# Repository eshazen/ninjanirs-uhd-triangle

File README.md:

# ninjanirs-uhd-triangle

### 2026-07-27

Printing 10 pcs `...onshape/UHD_Assembly_Filled_2026-07-13.stl` with .08mm extra fine.

(the other ones are still in the car)

### 2026-07-13

Printing `...onshape/UHD_Assembly_Filled_2026-07-13.stl` with .08mm extra fine.

40m time.

David wants 25 pcs.

### 2026-06-04

Printing UHD_Assembly_Filled
<br>This version has a "hull" shape around the optodes for (much) faster printing and no support headaches

Orient with light pipes facing up, tree support
<br>Two versions:  Standard, and 0.08mm fine

### 2026-05-06

Now working on solid triad for "production" for mechanical test.
<br>See `UHD_Assembly_Filled` in onshape.  Needs a new sketch which
defines a convex hull around the optode features to fill in the body.
Also need to fill the volume below the springtop with a pyramid-like
solid.

Really we need an algorithm which would traverse a range of Z and
generate a 3D hull formed by a 2D hull at each Z.

### 2026-03-20

* Printing second springtop (still 1-up).
<br>Printed two groups of 3 so total (8) pieces now (1 fail so 7 total)
* Printing (4) grommets with brim (2:14)  OK.

### 2026-03-18

Starting production print (some R&D first).
<br>Printing UHD_Assembly_Ver1 as is using 0.4mm nozzle
and profile "0.08mm Extra Fine".  Quoted time 42m.
<br>_If this doesn't work we'll change to 0.2mm nozzle._

Seems OK.  Printing Grommets with same settings.
Also seems ok with some cleanup.

Printing springtop both ways up, same settings.  Broke both but
right-side up seems best if we can manage to get it off the support.
<br>Trying again right-side up.  OK with care

Printing caps with same settings (right-side up).
<br>Caps don't quite fit in springtop.

#### Re-printing all with 0.2mm nozzle

* Printing grommets using "0.06mm High Quality".  Time est 38min
<br>Fails with non-adhered parts

Make some changes as AI suggests:

* Change first layer height to 0.16mm.
* Change bed temp from 55 to 60 for both first and subsequent layers
* Change initial layer speed to 20mm/s
  <br>(in Filament profile)

Did not (yet) try to scrub the plate with dish soap!

Print the grommets again, much better.

Now the optodes, same settings.  Est 1:07.  Ok.

And the caps.  45min.  OK

Springtop:  enlarge hole to 3.75 and drill through the arms.  26m
<br>Print failed (bad adhesion).  Cleaned plate and tried again.  Fail
<br>Change to "0.12mm Standard" and added one layer of raft.  Fail.

Probably need to print these with 0.5mm nozzle?  Or somehow create a raft?
<br>Or possibly it's the white filament?

Reset bed temp to 55 per Steve's suggestion.
<br>Clean bed with Dawn soap.  Add a brim.  Try again.  Success!

    Process -> objects -> Others -> Brim type "Outer brim"

Springtop now fits OK.

### 2025-11-23

Re-starting project.  Opened UHD_Assembly_Ver1 on Onshape.
The groove depth 0.75 was missing, add it somewhat arbitrarily.

<pre>
   1.9
+--------+
|        |
|        |
|        |
|     .75|
|    +---+ 
|    |     0.57
|    +---+ 
|        | 0.5
+--------+
</pre>

Attempting to print with 0.2mm nozzle, preset
<br>0.06mm High Quality @BBL X1C 0.2 nozzle
<br>Rotate so attach peg is up on build plate
<br>This is a 37m print for one, with support

Fix the slot, print again with "Tree Slim" support,
right-side up this time.

<pre>
   1.9
+--------+
|        |
|        |
|        |
|     .3 |
|    +---+ 
|    |     1
|    +---+ 
|        | 0.5
+--------+
</pre>

This seems better.  Also printed a copy of `test_pegs` and a set of optodes.

## 2025-06-10

Working on attachment to ninjaCap.  Trying some small retaining rings
from McMaster:

| Item | P/N       | OD    | Groove wid | Groove dia |
|------|-----------|-------|------------|------------|
| 1    | 98410A111 | 1/8"  | .012"      | .117"      |
| 2    | 98410A815 | 5/32" | .012"      | .146"      |
| 3    | 98410A110 | 3/16" | .018"      | .175"      |

Printing a test peg for number 3 (A110)

* Peg dia = 0.177
* groove wid = 0.018
* grove dia = 0.168

Using 0.2mm nozzle
<br>Profile "0.06mm High Quality @BBL X1C 0.2 nozzle"

Fits nicely, but clip probably not wide enough to secure to flexible
cap.  Maybe a plastic or metal washer under the clip?

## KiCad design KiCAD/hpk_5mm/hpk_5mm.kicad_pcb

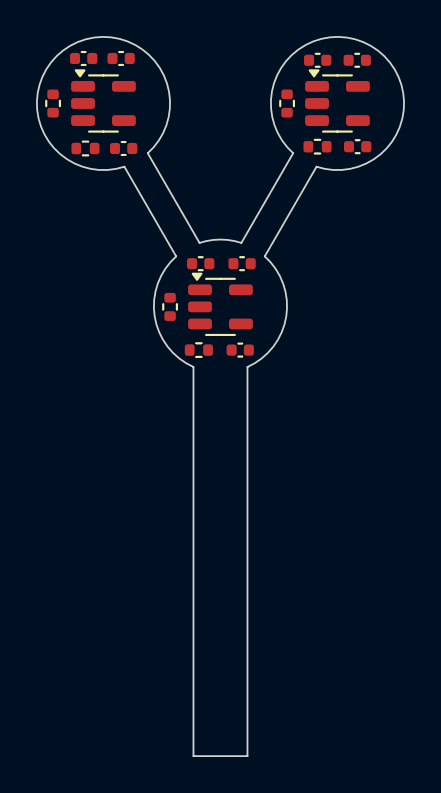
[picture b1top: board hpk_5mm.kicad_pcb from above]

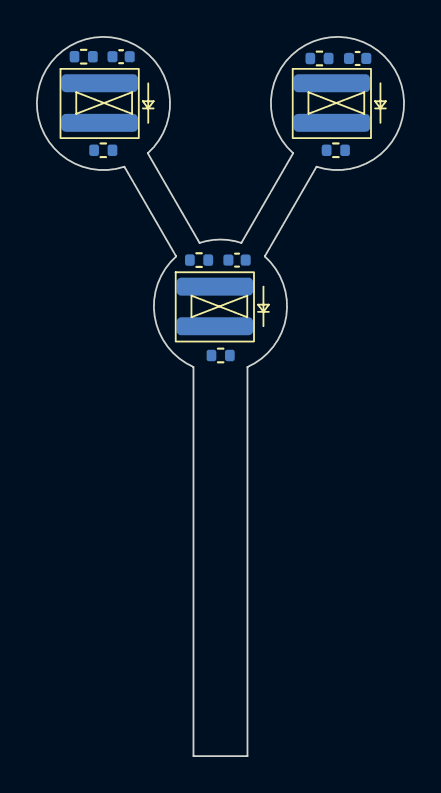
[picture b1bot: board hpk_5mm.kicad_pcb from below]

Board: 2 copper layers, 20.4 x 40.0 mm, 30 parts (12 on the bottom side), 13 nets, no tracks yet.

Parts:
C1, C2, C3, C4, C5, C6, C7, C8, C9, C10, C11, C12: 0.1uF; C_0402_1005Metric
D1, D2, D3: S13360-3050PE; s13360-3050pe
R1, R2, R3, R4, R5, R6, R7, R8, R9, R10, R11, R12: 1k; R_0402_1005Metric
U1, U2, U3: OPA810xDBV; SOT-23-5

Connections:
/sipm_tia1/V+: C2.1, C6.1, C10.1, U1.5 (V+), U2.5 (V+), U3.5 (V+)
/sipm_tia1/V-: C4.1, C8.1, C12.1, U1.2 (V-), U2.2 (V-), U3.2 (V-)
/sipm_tia1/VBIAS: R1.1, R5.1, R9.1
GND: C1.2, C2.2, C4.2, C5.2, C6.2, C8.2, C9.2, C10.2, C12.2, R2.1, R6.1, R10.1, U1.3 (+), U2.3 (+), U3.3 (+)
unnamed: C3.2, R3.2, R4.1, U1.1
unnamed: C7.2, R7.2, R8.1, U2.1
unnamed: C11.2, R11.2, R12.1, U3.1
unnamed: C3.1, D1.2 (A), R2.2, R3.1, U1.4 (-)
unnamed: C1.1, D1.1 (K), R1.2
unnamed: C7.1, D2.2 (A), R6.2, R7.1, U2.4 (-)
unnamed: C5.1, D2.1 (K), R5.2
unnamed: C11.1, D3.2 (A), R10.2, R11.1, U3.4 (-)
unnamed: C9.1, D3.1 (K), R9.2

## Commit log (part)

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2025-01-14 3D stuff to print
2025-01-15 3D design
2025-01-15 new 3D model with spring
2025-01-21 ready to print 3X model with reinforced spring attach
2025-01-26 working on hollow optode and HPK SiPM
2025-01-27 adding TIA for test layout
2025-01-28 trial 3-channel flexi
2025-01-28 trial 3-ch layout
2025-01-29 flexi design
2025-02-27 tweaking for 3d print at home
2025-02-27 reduce size of spring attach
2025-03-31 flex protots
2025-05-02 tweaking hollow optodes
2025-05-02 prep for new prints
2025-05-05 working on optode
2025-05-05 move optode floor up and fix slots to match
2025-05-06 tweak settings for printing
2025-05-29 As built with 13mm spacing for NIRX demo
2025-05-29 Change to 12mm pitch and add retainer clip
2025-06-11 working on packing/cap
2025-06-11 add cap option
2025-06-16 tweaking optode
2025-06-16 adjust patch geometry
2025-06-17 working on DB new lattice options
2025-06-18 working on new hex
2025-06-18 new hex
2025-06-18 hex ok, missing source optode grommet mount
2025-06-24 small tweaks
2025-06-24 new lattice
2025-06-25 David's new lattice
2025-06-25 refining new hex
2025-06-30 working on test peg
2025-10-11 add SK first try
2026-03-18 lots of updates, including 'final' printables
2026-03-19 README. Springtop print fails
2026-03-24 reduce cap height from 4.5 to 3
2026-04-02 as printed
2026-06-04 Update README with new version information
